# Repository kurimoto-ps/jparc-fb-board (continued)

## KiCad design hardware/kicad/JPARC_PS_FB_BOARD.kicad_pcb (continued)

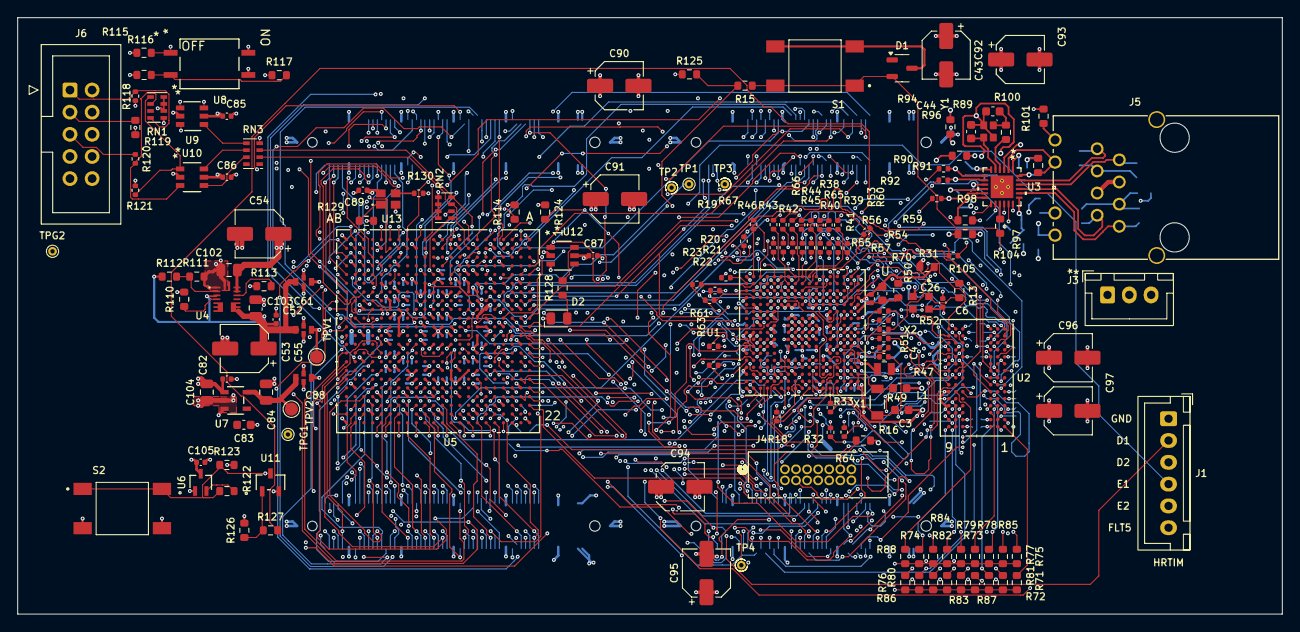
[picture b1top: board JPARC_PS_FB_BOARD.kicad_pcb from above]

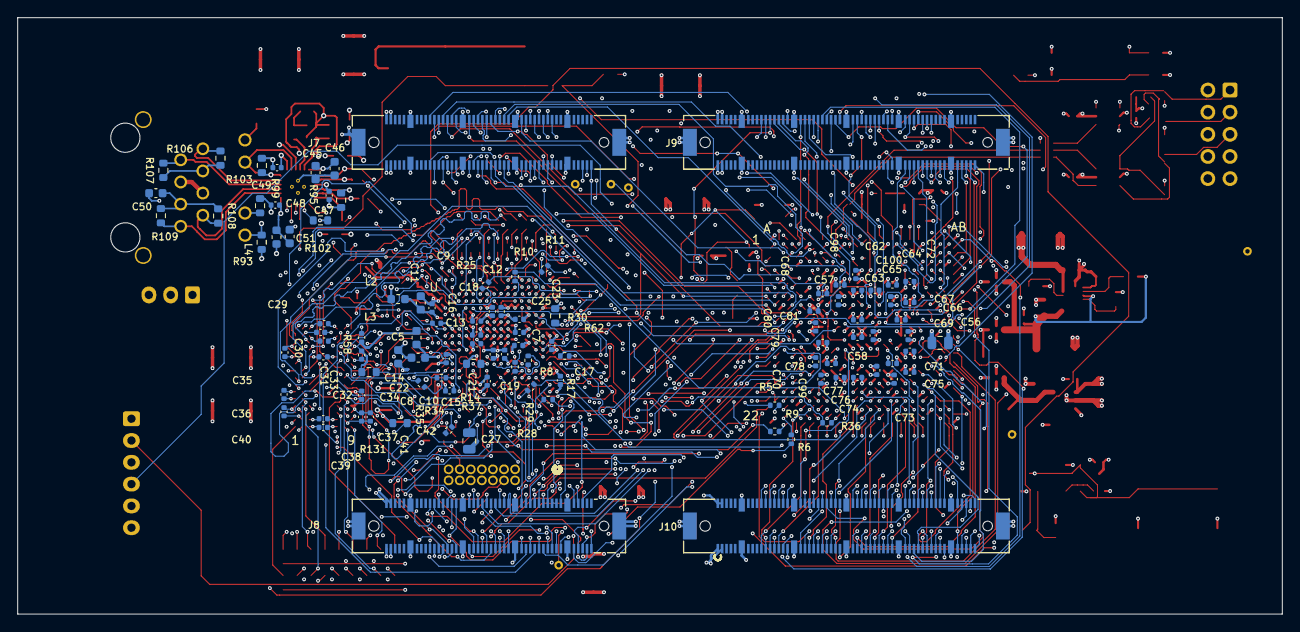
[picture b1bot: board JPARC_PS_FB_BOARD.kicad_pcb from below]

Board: 8 copper layers, 145.1 x 68.4 mm, 267 parts (106 on the bottom side), 469 nets.

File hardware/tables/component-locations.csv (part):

Reference,Value,X_mm,Y_mm,Rotation_deg,Side
C10,220pF,131.9,91.8,90.0,B.Cu
C100,100n,80.92,85.16,-90.0,B.Cu
C101,100n,80.72,92.36,0.0,B.Cu
C102,22u,60.25,81.65,180.0,F.Cu
C103,22u,63.3,86.0,90.0,F.Cu
C104,4.7u,57.7,95.65,-90.0,F.Cu
C105,100n,57.0,103.7,0.0,F.Cu
C11,100n,133.53,86.0,90.0,B.Cu
C12,100n,126.6,86.4,-90.0,B.Cu
C13,100n,128.42,89.1,180.0,B.Cu
C14,10u,137.4,91.6,90.0,B.Cu
C15,100n,127.2,94.4,90.0,B.Cu
C16,100n,128.4,90.1,180.0,B.Cu
C17,100n,118.8,94.3,-90.0,B.Cu
C18,100n,128.4,87.5,180.0,B.Cu
C19,100n,125.2,91.3,90.0,B.Cu
C20,100n,125.6,86.4,-90.0,B.Cu
C21,100n,126.5,91.3,90.0,B.Cu
C22,10u,135.1,91.7,0.0,B.Cu
C23,100n,123.5,87.3,0.0,B.Cu
C24,100n,123.5,88.8,0.0,B.Cu
C25,100n,123.6,90.3,0.0,B.Cu
C26,1u,135.17,84.35,90.0,F.Cu
C27,4.7u,129.25,101.25,90.0,B.Cu
C28,100n,133.9,84.92,90.0,F.Cu
C29,100n,146.3,88.8,180.0,B.Cu
C3,18pF,137.4,97.7,0.0,F.Cu
C30,100n,145.9,87.8,0.0,B.Cu
C31,100n,145.9,89.8,0.0,B.Cu
C32,100n,146.0,91.6,0.0,B.Cu
C33,100n,141.6,89.4,90.0,B.Cu
C34,100n,141.6,91.4,-90.0,B.Cu
C35,100n,150.4,91.1,90.0,B.Cu
C36,100n,150.5,95.92,90.0,B.Cu
C37,100n,141.6,96.0,-90.0,B.Cu
C38,100n,146.0,98.7,0.0,B.Cu
C39,100n,146.0,99.7,0.0,B.Cu
C4,18pF,137.175,95.2,0.0,F.Cu
C40,100n,150.5,97.9,90.0,B.Cu
C41,100n,141.6,98.5,-90.0,B.Cu
C42,100n,140.6,98.5,-90.0,B.Cu
C43,5.6p,147.85,63.45,180.0,F.Cu
C44,5.6p,145.35,65.775,90.0,F.Cu
C45,1u,146.88,70.47,-90.0,B.Cu
C46,470p,144.7,70.01,-90.0,B.Cu
C47,100n,145.32,73.09,-90.0,B.Cu
C48,100n,151.5,74.2,0.0,B.Cu
C49,100n,151.3,69.9,0.0,B.Cu
C5,100n,133.0,87.75,180.0,B.Cu
C50,22n,165.2,72.83,0.0,B.Cu
C51,10u,149.85,77.8,90.0,B.Cu
C52,100n,65.65,87.3,90.0,F.Cu
C53,47u,62.0,90.65,180.0,F.Cu
C54,47u,63.7,77.5,180.0,F.Cu
C55,NFM18CC223R1C3D,68.8,88.5,0.0,F.Cu
C56,4.7u,75.25,90.0,180.0,B.Cu
C57,100n,86.92,85.16,-90.0,B.Cu
C58,100n,84.72,87.36,0.0,B.Cu
C59,100n,84.72,89.36,0.0,B.Cu
C6,100n,142.1,85.4,90.0,F.Cu
C60,100n,82.92,89.16,-90.0,B.Cu
C61,NFM18CC223R1C3D,68.8,83.0,0.0,F.Cu
C62,100n,84.92,82.16,90.0,B.Cu
C63,100n,84.72,83.96,180.0,B.Cu
C64,100n,80.72,83.36,0.0,B.Cu
C65,100n,82.72,83.96,0.0,B.Cu
C66,100n,78.72,85.36,0.0,B.Cu
C67,100n,79.72,87.36,180.0,B.Cu
C68,100n,88.72,84.36,0.0,B.Cu
C69,100n,78.92,89.16,-90.0,B.Cu
C7,1u,119.8,90.3,90.0,B.Cu
C70,100n,88.92,94.16,-90.0,B.Cu
C71,100n,78.72,90.96,0.0,B.Cu
C72,100n,78.72,82.96,180.0,B.Cu
C73,100n,80.52,94.16,-90.0,B.Cu
C74,100n,82.52,93.16,-90.0,B.Cu
C75,100n,78.72,93.36,0.0,B.Cu
C76,100n,84.72,93.96,0.0,B.Cu
C77,100n,86.72,93.96,0.0,B.Cu
C78,100n,88.72,89.96,0.0,B.Cu
C79,100n,89.52,92.16,-90.0,B.Cu
C8,1u,131.5,95.5,180.0,B.Cu
C80,100n,89.72,86.36,180.0,B.Cu
C81,100n,89.52,88.16,90.0,B.Cu
C82,100n,60.0,94.15,0.0,F.Cu
C83,1.5n,61.95,99.4,0.0,F.Cu
C84,4.7u,64.5,95.65,90.0,F.Cu
C85,100n,60.0,64.0,0.0,F.Cu
C86,100n,60.0,71.0,0.0,F.Cu
C87,100n,102.0,80.0,0.0,F.Cu
C88,NFM18CC223R1C3D,68.8,94.0,0.0,F.Cu
C89,100n,75.6,72.5,180.0,F.Cu
C9,1u,134.82,85.41,90.0,B.Cu
C90,47u,105.0,60.5,0.0,F.Cu
C91,47u,104.5,73.5,0.0,F.Cu
C92,47u,142.5,57.0,-90.0,F.Cu
C93,47u,151.0,57.5,0.0,F.Cu
C94,47u,112.0,106.5,0.0,F.Cu
C95,47u,115.0,116.4,90.0,F.Cu
C96,47u,156.5,91.7,0.0,F.Cu
C97,47u,156.5,97.8,0.0,F.Cu
C98,100n,86.72,83.36,180.0,B.Cu
C99,100n,87.72,92.36,0.0,B.Cu
D1,"MMBZ6V2AL,215",137.4375,58.5,0.0,F.Cu
D2,LED,98.1,87.2,0.0,F.Cu
J1,B6B-XH-A(LF)(SN),168.0,98.7,-90.0,F.Cu
J10,FX10A-100P/10-SV1(71) / CN1C,86.0,111.0,90.0,B.Cu
J3,B3B-XH-A(LF)(SN),161.0,84.5,0.0,F.Cu
J4,3220-14-0100-00,124.0,104.5,0.0,F.Cu
J5,934635206,162.349999,76.63,90.0,F.Cu
J6,61201021621,42.0,61.0,0.0,F.Cu
J7,FX10A-80P/8-SV1(71),127.0,67.0,90.0,B.Cu
J8,FX10A-80P/8-SV1(71),127.0,111.0,90.0,B.Cu
J9,FX10A-100P/10-SV1(71) / CN1D,86.0,67.0,90.0,B.Cu
L1,DFE201210U-2R2M=P2,135.4,93.0,180.0,F.Cu
L2,BBGK00160808601Y00,137.42,84.98,0.0,B.Cu
L3,FBMJ1608HM180NTR,135.3,89.4,-90.0,B.Cu
L4,600R@100 MHz,151.36,77.87,90.0,B.Cu
R10,33R,124.0,82.4,-90.0,B.Cu
R100,330R,153.66,64.01,90.0,F.Cu
R101,10K,153.04,69.65,-90.0,F.Cu
R102,10K,146.32,75.95,0.0,B.Cu
R103,12K1,153.04,69.65,90.0,B.Cu
R104,0R,148.68,76.62,-90.0,F.Cu
R105,33R,143.32,80.0,180.0,F.Cu
R106,49R9,157.79,68.815,90.0,B.Cu
R107,49R9,164.34,70.21,90.0,B.Cu
R108,49R9,158.05,75.45,-90.0,B.Cu
R109,49R9,164.62,75.415,-90.0,B.Cu
R11,33R,120.600001,81.500001,-45.0,B.Cu
R110,100K,55.1,85.0,90.0,F.Cu
R111,200K,56.55,82.4,0.0,F.Cu
R112,200K,53.4,82.4,0.0,F.Cu
R113,100K,64.25,83.5,0.0,F.Cu
R114,4.7K,93.0,75.0,90.0,F.Cu
R115,4.7K,50.5,56.73,0.0,F.Cu
R116,4.7K,50.5,59.27,0.0,F.Cu
R117,1K,66.0,59.3,0.0,F.Cu
R118,47R,49.5,61.7,90.0,F.Cu
R119,0R,49.5,65.3,90.0,F.Cu
R120,47R,49.5,68.9,90.0,F.Cu
R121,47R,49.5,72.5,90.0,F.Cu
R122,0R,60.0,107.0,0.0,F.Cu
R123,4.7K,60.0,104.0,0.0,F.Cu
R124,1K,96.5,75.0,90.0,F.Cu
R125,0R,113.05,59.2,0.0,F.Cu
R126,47K,62.0,111.5,90.0,F.Cu
R127,1K,65.0,111.5,0.0,F.Cu
R128,1K,98.5,83.7,90.0,F.Cu
R129,4.7K,76.0,76.0,0.0,F.Cu
R13,10K,144.0,84.0,-90.0,F.Cu
R130,33R,82.0,72.85,180.0,F.Cu
R131,10K,137.2,99.2,0.0,B.Cu
R14,10K,128.745,92.405,0.0,B.Cu
R15,0R,119.425,60.5,180.0,F.Cu
R16,100R,133.0,101.2,0.0,F.Cu
R17,33R,122.5,92.0,90.0,B.Cu
R18,33R,123.06,98.46,-90.0,F.Cu
R19,33R,120.4,76.43,90.0,F.Cu
R20,33R,117.23,82.52,180.0,F.Cu
R21,33R,113.9,83.31,180.0,F.Cu
R22,33R,115.36,85.1,180.0,F.Cu
R23,33R,115.98,84.0,180.0,F.Cu
R25,33R,127.4,83.4,135.0,B.Cu
R28,33R,122.2,95.1,135.0,B.Cu
R29,33R,124.0,92.75,90.0,B.Cu
R30,0R,119.4,86.9,-90.0,B.Cu
R31,0R,140.3,81.3,0.0,F.Cu
R32,33R,130.81,100.24,-90.0,F.Cu
R33,33R,129.23,97.42,-90.0,F.Cu
R34,33R,132.45,94.0,180.0,B.Cu
R35,33R,134.75,94.7,-135.0,B.Cu
R36,33R,88.22,99.16,0.0,B.Cu
R37,33R,131.6,100.0,135.0,B.Cu
R38,33R,125.9,76.46,90.0,F.Cu
R39,33R,126.98,76.47,90.0,F.Cu
R40,33R,126.0,79.09,90.0,F.Cu
R41,33R,127.02,79.09,90.0,F.Cu
R42,33R,123.82,79.07,90.0,F.Cu
R43,33R,124.89,79.08,90.0,F.Cu
R44,33R,124.83,76.46,90.0,F.Cu
R45,33R,123.76,76.45,90.0,F.Cu
R46,33R,122.69,79.08,90.0,F.Cu
R47,33R,135.35,90.55,0.0,F.Cu
R48,33R,135.35,89.5,0.0,F.Cu
R49,33R,135.35,91.6,0.0,F.Cu
R5,33R,94.22,97.16,0.0,B.Cu
R50,33R,135.35,86.35,0.0,F.Cu
R51,33R,135.35,87.4,0.0,F.Cu
R52,33R,135.36,88.45,0.0,F.Cu
R53,33R,129.04,76.48,90.0,F.Cu
R54,33R,131.16,79.12,90.0,F.Cu
R55,33R,128.05,79.1,90.0,F.Cu
R56,33R,129.07,79.12,90.0,F.Cu
R57,33R,130.1,79.11,90.0,F.Cu
R58,0R,140.75,93.35,180.0,B.Cu
R59,33R,133.4,77.2,45.0,F.Cu
R6,33R,92.32,101.06,-90.0,B.Cu
R60,33R,130.07,76.48,90.0,F.Cu
R61,33R,115.83,90.4,180.0,F.Cu
R62,33R,118.3,91.5,0.0,B.Cu
R63,33R,115.82,92.57,180.0,F.Cu
R64,33R,129.23,100.26,-90.0,F.Cu
R65,33R,128.01,76.48,90.0,F.Cu
R66,33R,122.69,76.44,90.0,F.Cu
R67,33R,119.3,78.35,90.0,F.Cu
R70,0R,137.0,84.0,-90.0,F.Cu
R71,10K,150.6,117.5,90.0,F.Cu
R72,10K,149.0,117.5,90.0,F.Cu
R73,10K,142.6,114.5,90.0,F.Cu
R74,10K,139.4,114.5,90.0,F.Cu
R75,10K,150.6,114.5,90.0,F.Cu
R76,10K,137.8,117.5,90.0,F.Cu
R77,10K,149.0,114.5,90.0,F.Cu
R78,10K,145.8,114.5,90.0,F.Cu
R79,10K,144.2,114.5,90.0,F.Cu
R8,33R,120.200001,96.499999,0.0,B.Cu
R80,10K,141.0,117.5,90.0,F.Cu
R81,10K,147.4,117.5,90.0,F.Cu
R82,10K,144.2,117.5,90.0,F.Cu
R83,10K,142.6,117.5,90.0,F.Cu
R84,10K,141.0,114.5,90.0,F.Cu
R85,10K,147.4,114.5,90.0,F.Cu
R86,10K,139.4,117.5,90.0,F.Cu
R87,10K,145.8,117.5,90.0,F.Cu
R88,10K,137.8,114.5,90.0,F.Cu
R89,0R,149.35,65.85,90.0,F.Cu
R9,33R,94.22,100.16,0.0,B.Cu
R90,33R,142.19,70.02,0.0,F.Cu
R91,33R,142.16,71.34,0.0,F.Cu
R92,33R,141.42,73.44,0.0,F.Cu
R93,10K,153.06,78.46,90.0,B.Cu
R94,10K,142.98,65.23,-90.0,F.Cu
R95,10K,143.95,73.64,-90.0,B.Cu
R96,10K,144.015,68.54,180.0,F.Cu
R97,10K,144.68,77.54,180.0,F.Cu
R98,1K5,144.67,75.95,180.0,F.Cu
R99,330R,153.25,74.27,-90.0,B.Cu
RN1,4-4.7K,52.0,63.0,0.0,F.Cu
RN2,4-4.7K,85.0,74.5,0.0,F.Cu
RN3,4-47R,63.0,68.3,0.0,F.Cu
S1,TS04-66-55-BK-160-SMT,127.45,58.25,180.0,F.Cu
S2,TS04-66-55-BK-160-SMT,48.0,109.0,0.0,F.Cu
TP1,~,113.0,71.8,0.0,F.Cu
TP2,~,111.0,72.2,0.0,F.Cu
TP3,~,117.1,71.8,0.0,F.Cu
TP4,~,119.0,115.5,0.0,F.Cu
TPG1,~,67.0,100.5,0.0,F.Cu
TPG2,~,40.0,79.5,0.0,F.Cu
TPV1,~,70.3,91.6,0.0,F.Cu
TPV2,~,67.4,97.6,0.0,F.Cu
U1,STM32H745XIH6,126.0,88.8,180.0,F.Cu
U10,SN74LVC2G17DBVTG4,56.0,71.0,0.0,F.Cu
U11,2N7002_215,65.0,106.0,0.0,F.Cu
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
